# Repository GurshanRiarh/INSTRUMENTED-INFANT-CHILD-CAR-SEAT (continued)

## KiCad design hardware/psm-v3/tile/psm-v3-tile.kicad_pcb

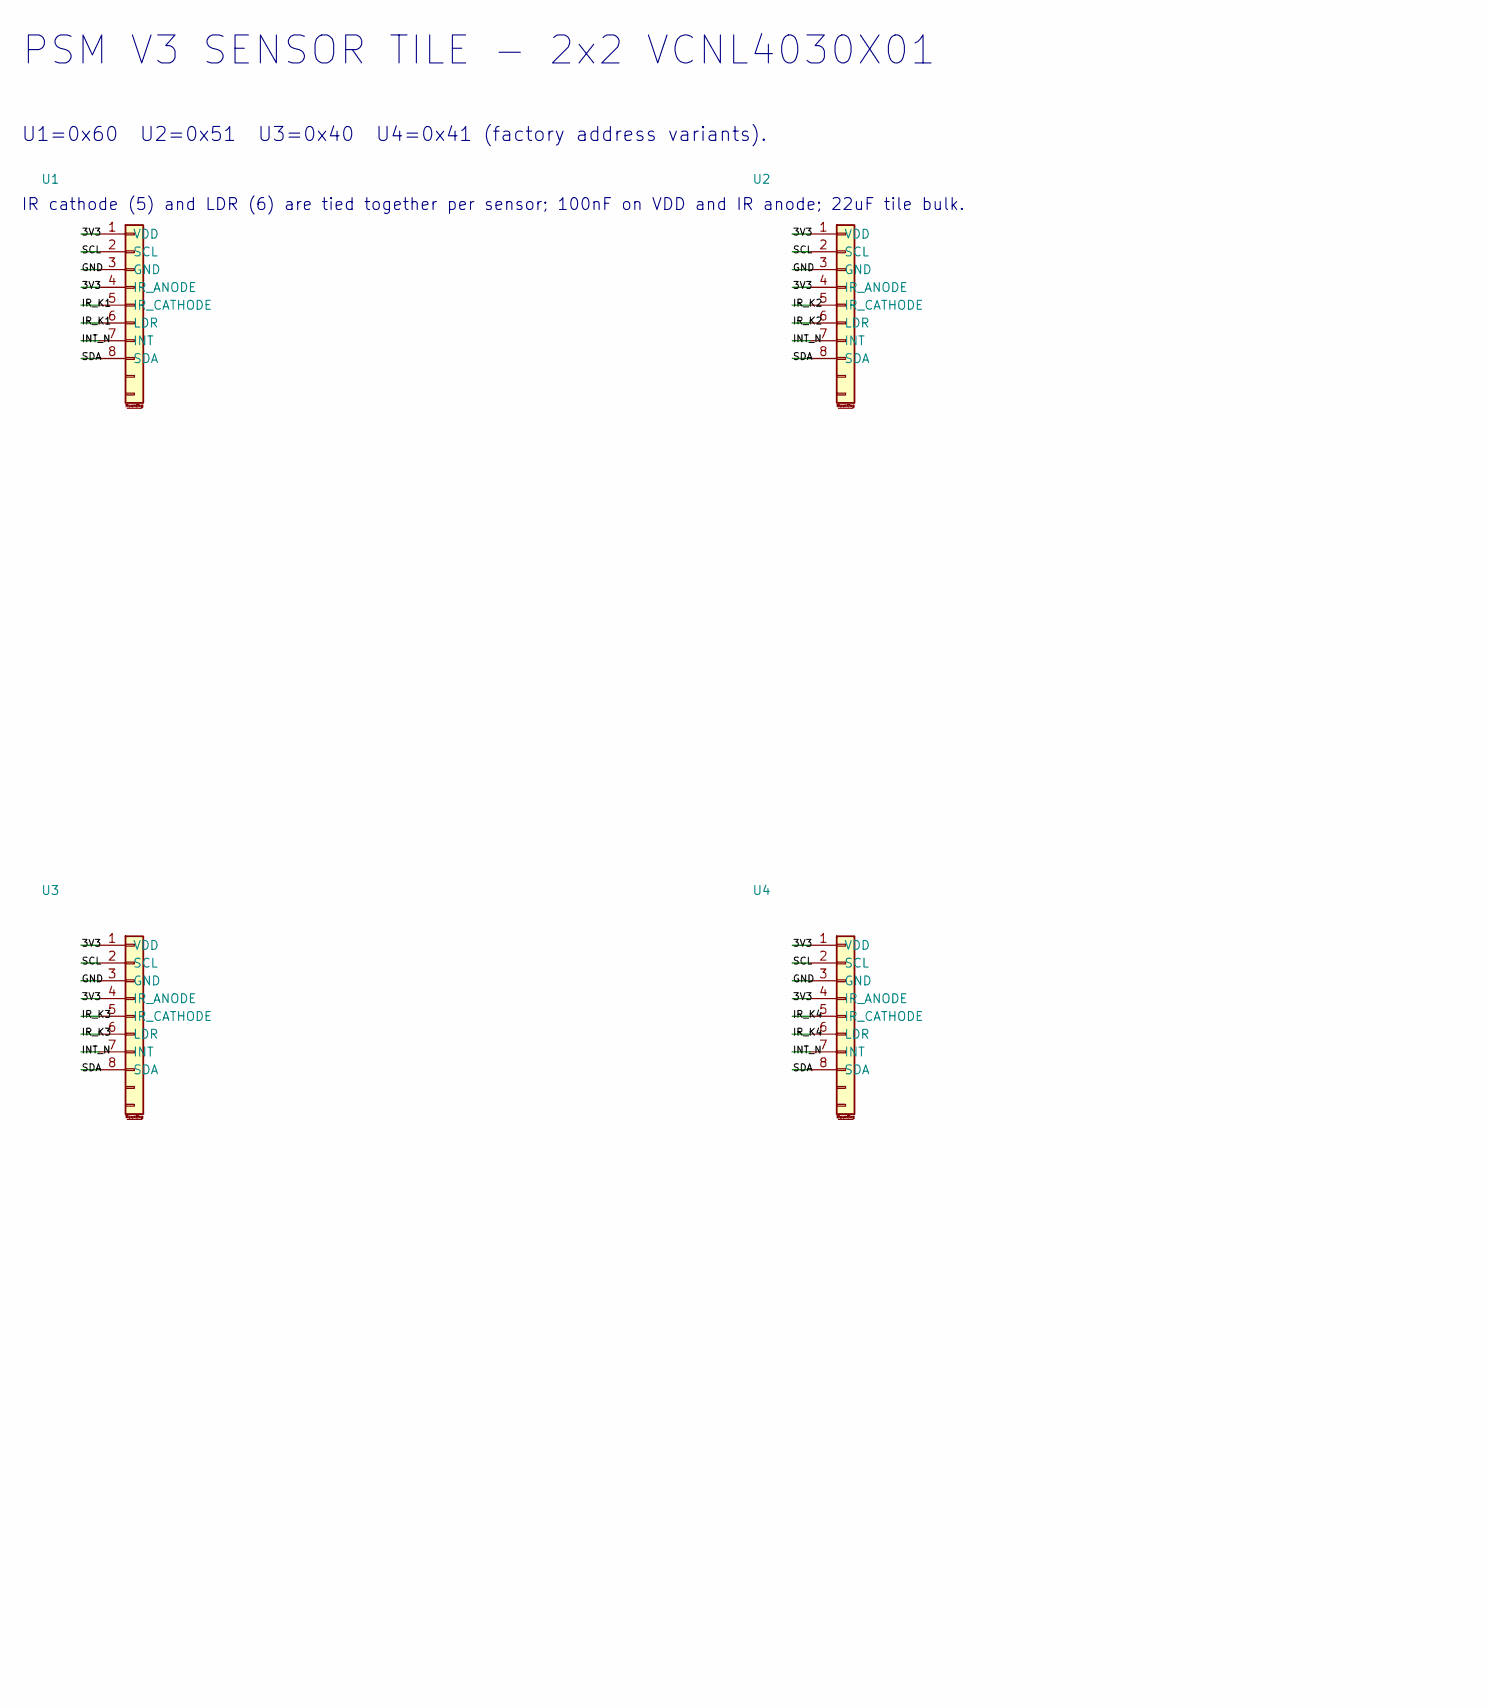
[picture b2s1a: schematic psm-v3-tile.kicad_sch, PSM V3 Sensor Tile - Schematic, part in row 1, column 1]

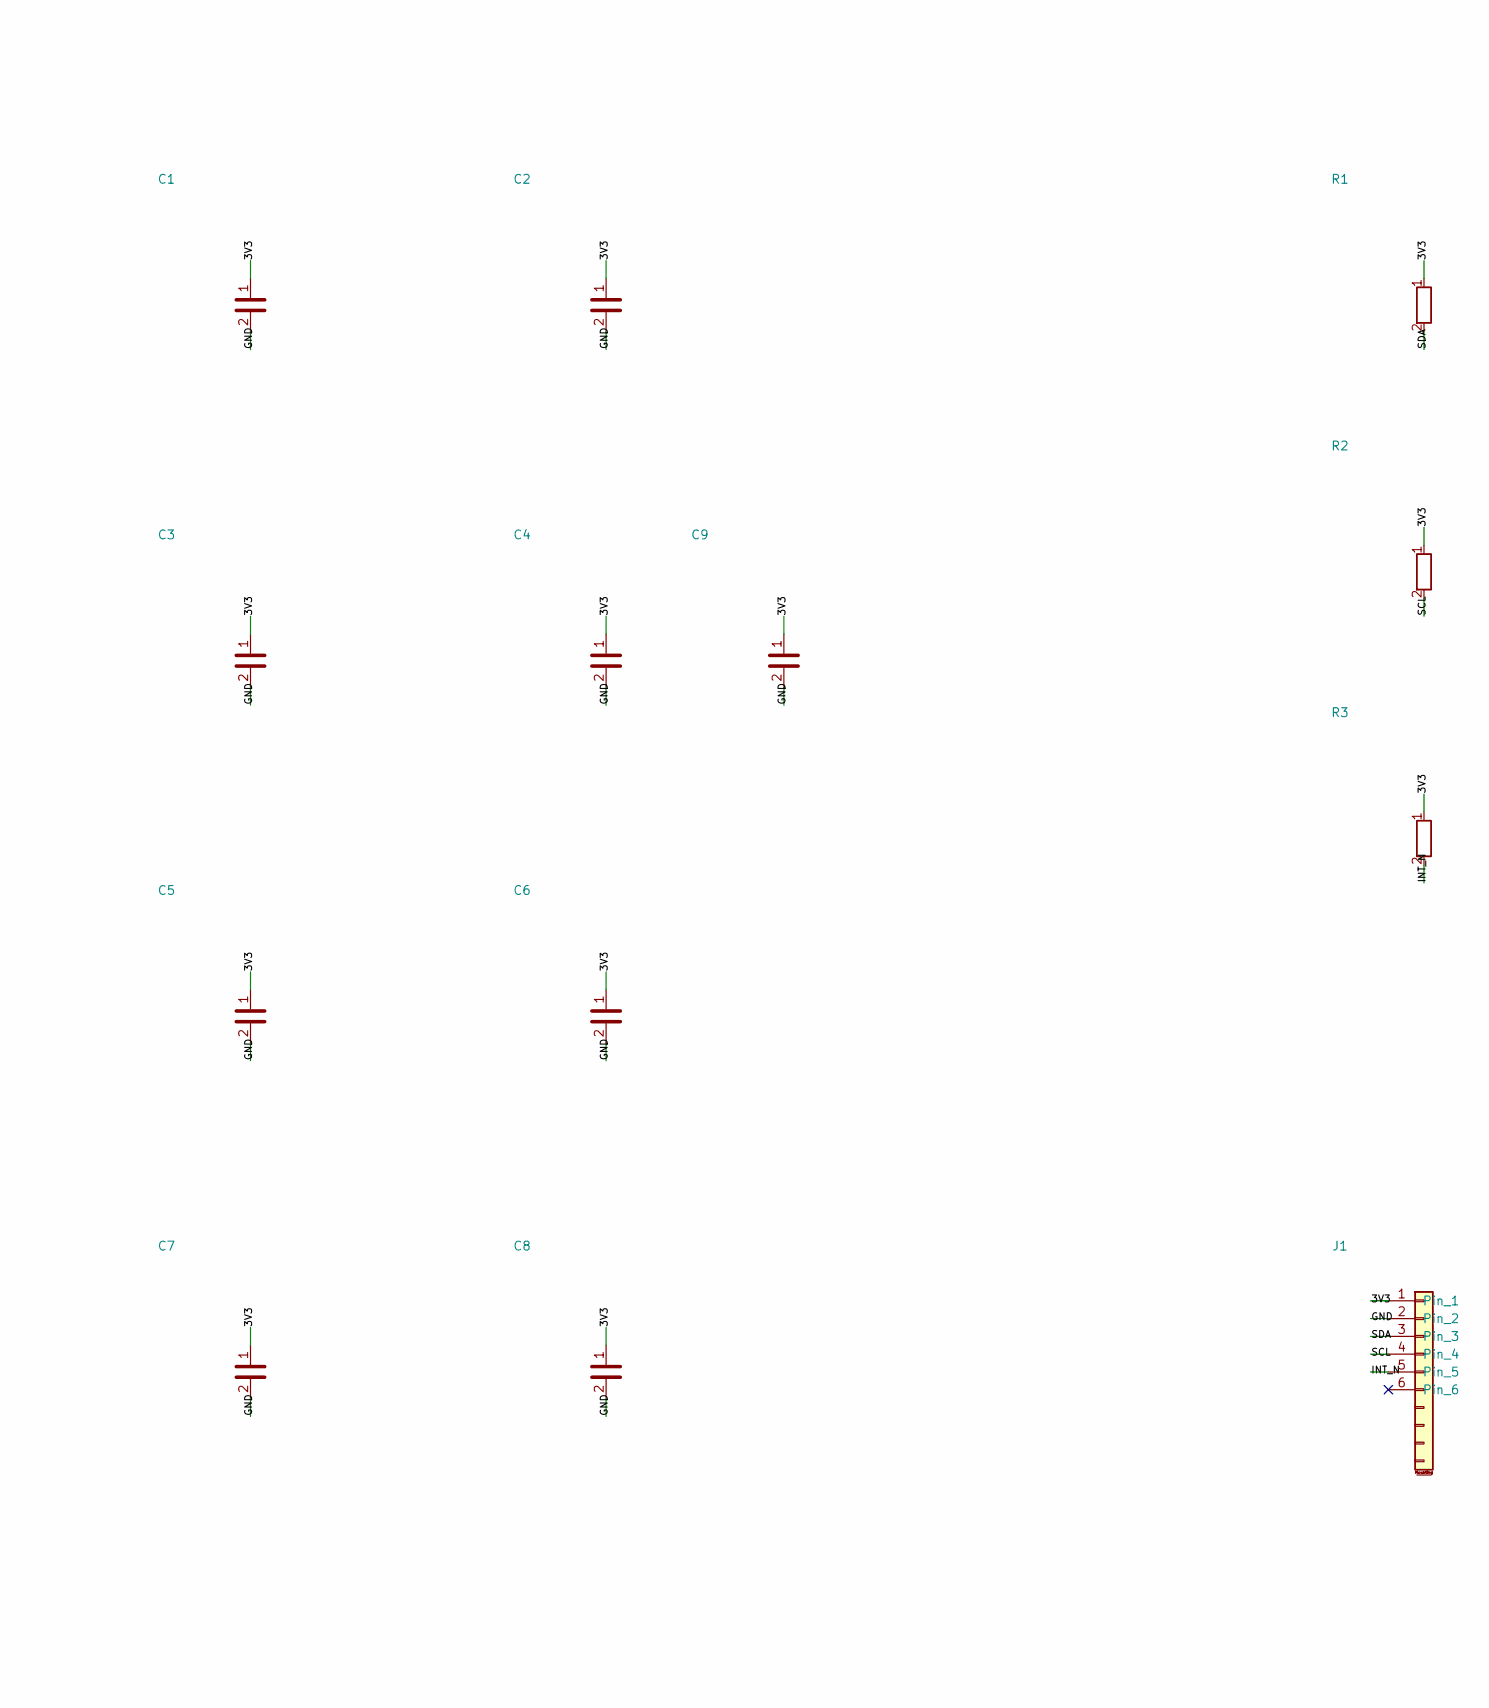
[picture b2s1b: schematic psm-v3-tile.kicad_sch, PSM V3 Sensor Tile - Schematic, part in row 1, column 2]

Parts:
C1, C2, C3, C4, C5, C6, C7, C8: 100n; C_0603_1608Metric; Part Description 0.1uF 10% 16V Ceramic Capacitor X7R 040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
C9: 22u; C_0805_2012Metric; Part Description 0.1uF 10% 16V Ceramic Capacitor X7R 040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
J1: TILE_IF; PinHeader_1x06_P1.27mm_Vertical
R1, R2, R3: 10k; R_0603_1608Metric
U1: VCNL4030X01 0x60; VCNL4030X01
U2: VCNL4030X01 0x51; VCNL4030X01
U3: VCNL4030X01 0x40; VCNL4030X01
U4: VCNL4030X01 0x41; VCNL4030X01

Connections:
3V3: C1.1, C2.1, C3.1, C4.1, C5.1, C6.1, C7.1, C8.1, C9.1, J1.1, R1.1, R2.1, R3.1, U1.1 (VDD), U1.4 (IR_ANODE), U2.1 (VDD), U2.4 (IR_ANODE), U3.1 (VDD), U3.4 (IR_ANODE), U4.1 (VDD), U4.4 (IR_ANODE)
GND: C1.2, C2.2, C3.2, C4.2, C5.2, C6.2, C7.2, C8.2, C9.2, J1.2, U1.3 (GND), U2.3 (GND), U3.3 (GND), U4.3 (GND)
INT_N: J1.5, R3.2, U1.7 (INT), U2.7 (INT), U3.7 (INT), U4.7 (INT)
IR_K1: U1.5 (IR_CATHODE), U1.6 (LDR)
IR_K2: U2.5 (IR_CATHODE), U2.6 (LDR)
IR_K3: U3.5 (IR_CATHODE), U3.6 (LDR)
IR_K4: U4.5 (IR_CATHODE), U4.6 (LDR)
SCL: J1.4, R2.2, U1.2 (SCL), U2.2 (SCL), U3.2 (SCL), U4.2 (SCL)
SDA: J1.3, R1.2, U1.8 (SDA), U2.8 (SDA), U3.8 (SDA), U4.8 (SDA)

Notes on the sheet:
PSM V3 SENSOR TILE - 2x2 VCNL4030X01
U1=0x60 U2=0x51 U3=0x40 U4=0x41 (factory address variants).
IR cathode (5) and LDR (6) are tied together per sensor; 100nF on VDD and IR anode; 22uF tile bulk.
J1: 1=3V3 2=GND 3=SDA 4=SCL 5=INT_N 6=NC. Sealing ring and conformal coat are PCB-level.

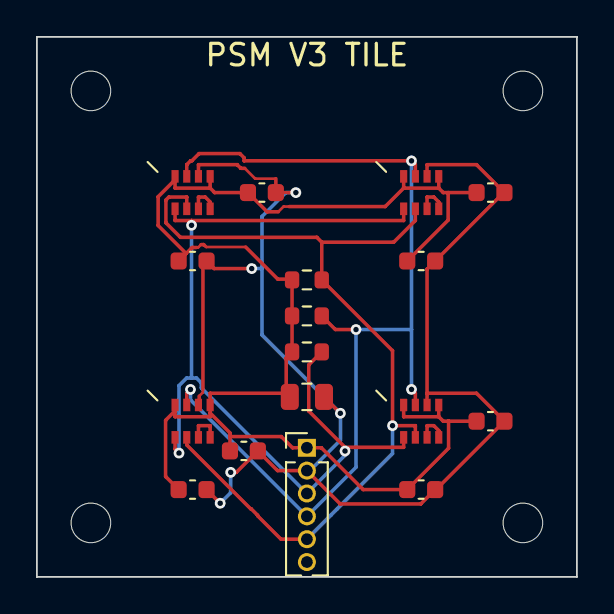
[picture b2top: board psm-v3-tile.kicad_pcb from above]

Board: 2 copper layers, 30.0 x 30.0 mm, 21 parts (0 on the bottom side), 9 nets.

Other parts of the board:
H1, H2, H3, H4: M2; MountingHole_2.2mm_M2

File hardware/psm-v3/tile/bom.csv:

Quantity,References,Value,Footprint
8,C1 C2 C3 C4 C5 C6 C7 C8,100n,C_0603_1608Metric
3,R1 R2 R3,10k,R_0603_1608Metric
1,C9,22u,C_0805_2012Metric
4,H1 H2 H3 H4,M2,MountingHole_2.2mm_M2
1,J1,TILE_IF,PinHeader_1x06_P1.27mm_Vertical
1,U3,VCNL4030X01 0x40,VCNL4030X01
1,U4,VCNL4030X01 0x41,VCNL4030X01
1,U2,VCNL4030X01 0x51,VCNL4030X01
1,U1,VCNL4030X01 0x60,VCNL4030X01

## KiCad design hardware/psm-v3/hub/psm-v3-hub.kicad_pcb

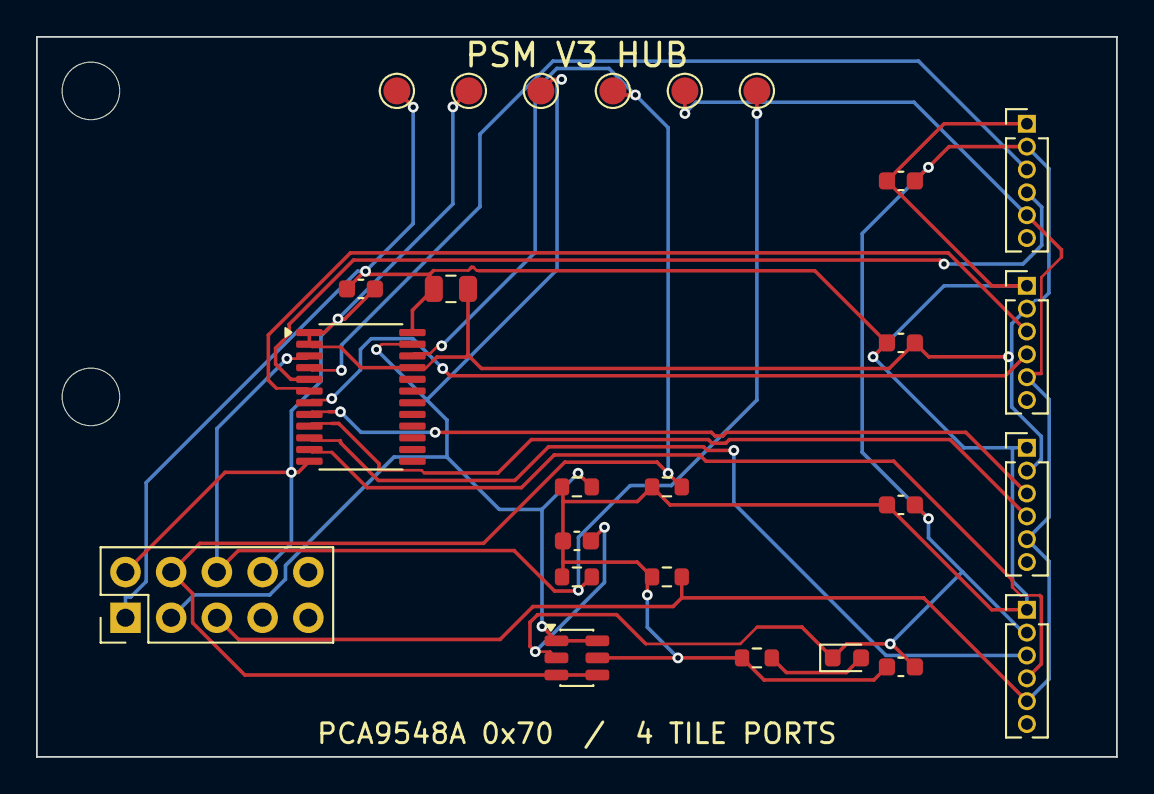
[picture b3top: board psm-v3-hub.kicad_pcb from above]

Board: 2 copper layers, 60.0 x 40.0 mm, 28 parts (0 on the bottom side), 15 nets.

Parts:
C1, C3, C4, C5, C6, C7: 100n; C_0603_1608Metric
C2: 10u; C_0805_2012Metric
D1: POWER; LED_0603_1608Metric
H1, H2: M3; MountingHole_3.2mm_M3
J1: HOST_IF; PinHeader_2x05_P2.54mm_Vertical
J2: TILE_0; PinHeader_1x06_P1.27mm_Vertical
J3: TILE_1; PinHeader_1x06_P1.27mm_Vertical
J4: TILE_2; PinHeader_1x06_P1.27mm_Vertical
J5: TILE_3; PinHeader_1x06_P1.27mm_Vertical
R1, R2: 2.2k; R_0603_1608Metric
R3, R4: 10k; R_0603_1608Metric
R5: 1k; R_0603_1608Metric
TP1: 3V3; TestPoint_Pad_D1.5mm
TP2: GND; TestPoint_Pad_D1.5mm
TP3: SDA; TestPoint_Pad_D1.5mm
TP4: SCL; TestPoint_Pad_D1.5mm
TP5: INT_N; TestPoint_Pad_D1.5mm
TP6: MUX_RST; TestPoint_Pad_D1.5mm
U1: PCA9548A; TSSOP-24_4.4x7.8mm_P0.65mm
U2: USBLC6-2SC6; SOT-23-6

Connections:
3V3: C1.1, C2.1, C3.1, C4.1, C5.1, C6.1, C7.1, J1.1, J2.1, J3.1, J4.1, J5.1, R1.1, R2.1, R3.1, R4.1, R5.1, TP1.1, U1.24, U2.5
GND: C1.2, C2.2, C3.2, C4.2, C5.2, C6.2, C7.2, D1.1, J1.2, J1.8, J2.2, J3.2, J4.2, J5.2, TP2.1, U1.1, U1.2, U1.12, U1.21, U2.2
INT_N: J1.5, J2.5, J3.5, J4.5, J5.5, R4.2, TP5.1
LED_A: D1.2, R5.2
MUX_RST: J1.6, R3.2, TP6.1, U1.3
SCL: J1.4, R2.2, TP4.1, U1.22, U2.3, U2.4
SCL_C0: J2.4, U1.5
SCL_C1: J3.4, U1.7
SCL_C2: J4.4, U1.9
SCL_C3: J5.4, U1.11
SDA: J1.3, R1.2, TP3.1, U1.23, U2.1, U2.6
SDA_C0: J2.3, U1.4
SDA_C1: J3.3, U1.6
SDA_C2: J4.3, U1.8
SDA_C3: J5.3, U1.10

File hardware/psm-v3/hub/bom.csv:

Quantity,References,Value,Footprint
6,C1 C3 C4 C5 C6 C7,100n,C_0603_1608Metric
2,R3 R4,10k,R_0603_1608Metric
1,C2,10u,C_0805_2012Metric
1,R5,1k,R_0603_1608Metric
2,R1 R2,2.2k,R_0603_1608Metric
1,TP1,3V3,TestPoint_Pad_D1.5mm
1,TP2,GND,TestPoint_Pad_D1.5mm
1,J1,HOST_IF,PinHeader_2x05_P2.54mm_Vertical
1,TP5,INT_N,TestPoint_Pad_D1.5mm
2,H1 H2,M3,MountingHole_3.2mm_M3
1,TP6,MUX_RST,TestPoint_Pad_D1.5mm
1,U1,PCA9548A,TSSOP-24_4.4x7.8mm_P0.65mm
1,D1,POWER,LED_0603_1608Metric
1,TP4,SCL,TestPoint_Pad_D1.5mm
1,TP3,SDA,TestPoint_Pad_D1.5mm
1,J2,TILE_0,PinHeader_1x06_P1.27mm_Vertical
1,J3,TILE_1,PinHeader_1x06_P1.27mm_Vertical
1,J4,TILE_2,PinHeader_1x06_P1.27mm_Vertical
1,J5,TILE_3,PinHeader_1x06_P1.27mm_Vertical
1,U2,USBLC6-2SC6,SOT-23-6
